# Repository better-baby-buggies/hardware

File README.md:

# hardware
Hardware designs for the PCB's in our Better Baby Buggy!

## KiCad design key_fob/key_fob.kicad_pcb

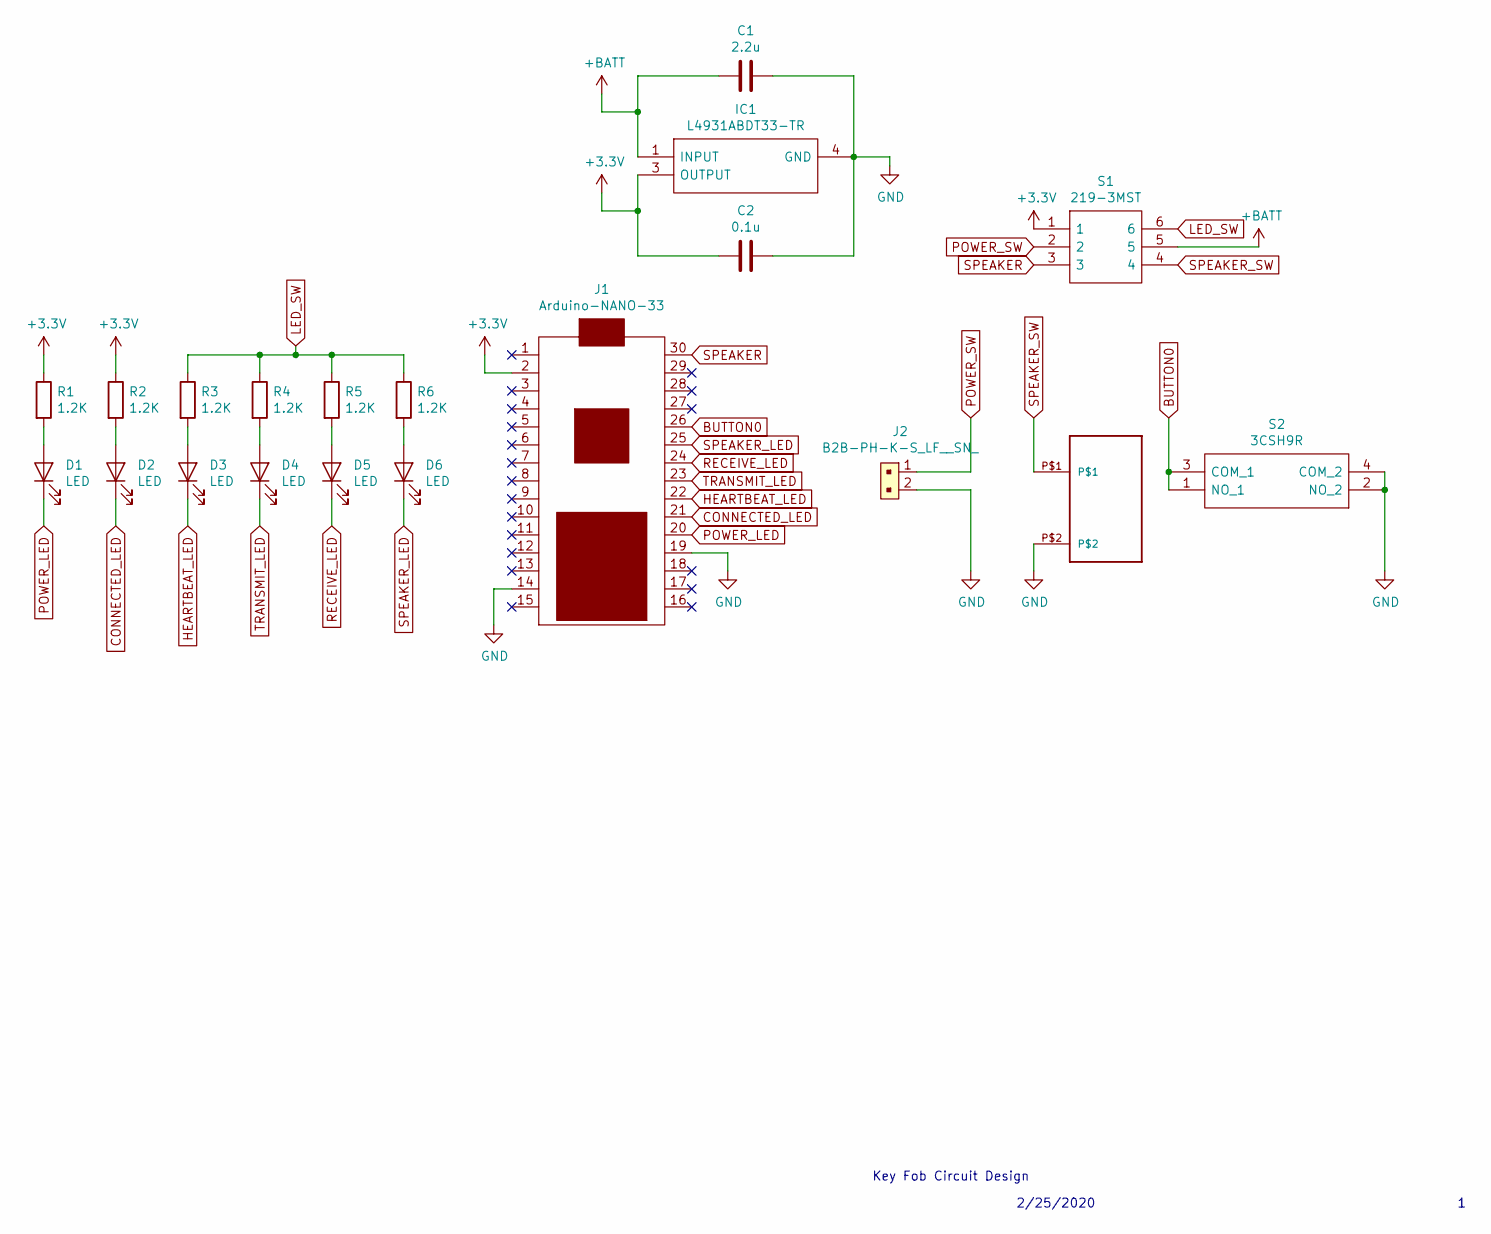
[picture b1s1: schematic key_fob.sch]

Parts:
C1: 2.2u; C_0603_1608Metric_Pad1.05x0.95mm_HandSolder
C2: 0.1u; C_0603_1608Metric_Pad1.05x0.95mm_HandSolder
D1, D2: LED; LED_D5.0mm
D3, D4, D5, D6: LED; LED_1206_3216Metric_Pad1.42x1.75mm_HandSolder
IC1: L4931ABDT33-TR; TO228P972X240-3N; Mouser Part Number 511-L4931ABDT33-TR
J1: Arduino-NANO-33; NANO_33_Footprint_SMD_Castell
J2: B2B-PH-K-S_LF__SN_; PinHeader_1x2_P2mm_Drill1mm; MPN B2B-PH-K-S(LF)(SN); Digi-Key_PN 455-1704-ND
R1, R2, R3, R4, R5, R6: 1.2K; R_0603_1608Metric_Pad1.05x0.95mm_HandSolder
S1: 219-3MST; SOP254P991X385-6N; Mouser Part Number 774-2193MST
S2: 3CSH9R; Mouser Part Number 642-3CSH9R
U1: PS1240P02BT

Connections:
+3V3: C2.1, IC1.3 (OUTPUT), J1.2, R1.1, R2.1, S1.1
+BATT: C1.2, IC1.1 (INPUT), S1.5
BUTTON0: J1.26, S2.1 (NO_1), S2.3 (COM_1)
CONNECTED_LED: D2.1 (K), J1.21
GND: C1.1, C2.2, IC1.4 (GND), J1.14, J1.19, J2.2, S2.2 (NO_2), S2.4 (COM_2), U1.P$2
HEARTBEAT_LED: D3.1 (K), J1.22
LED_SW: R3.1, R4.1, R5.1, R6.1, S1.6
unnamed: D1.2 (A), R1.2
unnamed: D2.2 (A), R2.2
unnamed: D3.2 (A), R3.2
unnamed: D4.2 (A), R4.2
unnamed: D5.2 (A), R5.2
unnamed: D6.2 (A), R6.2
POWER_LED: D1.1 (K), J1.20
POWER_SW: J2.1, S1.2
RECEIVE_LED: D5.1 (K), J1.24
SPEAKER: J1.30, S1.3
SPEAKER_LED: D6.1 (K), J1.25
SPEAKER_SW: S1.4, U1.P$1
TRANSMIT_LED: D4.1 (K), J1.23

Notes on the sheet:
Key Fob Circuit Design
2/25/2020

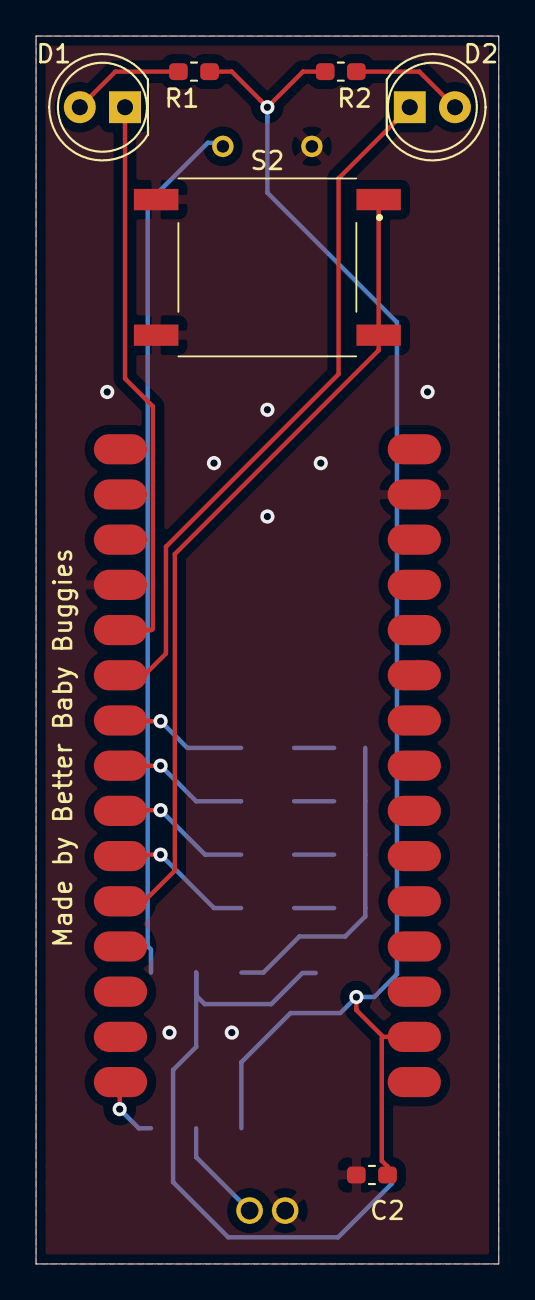
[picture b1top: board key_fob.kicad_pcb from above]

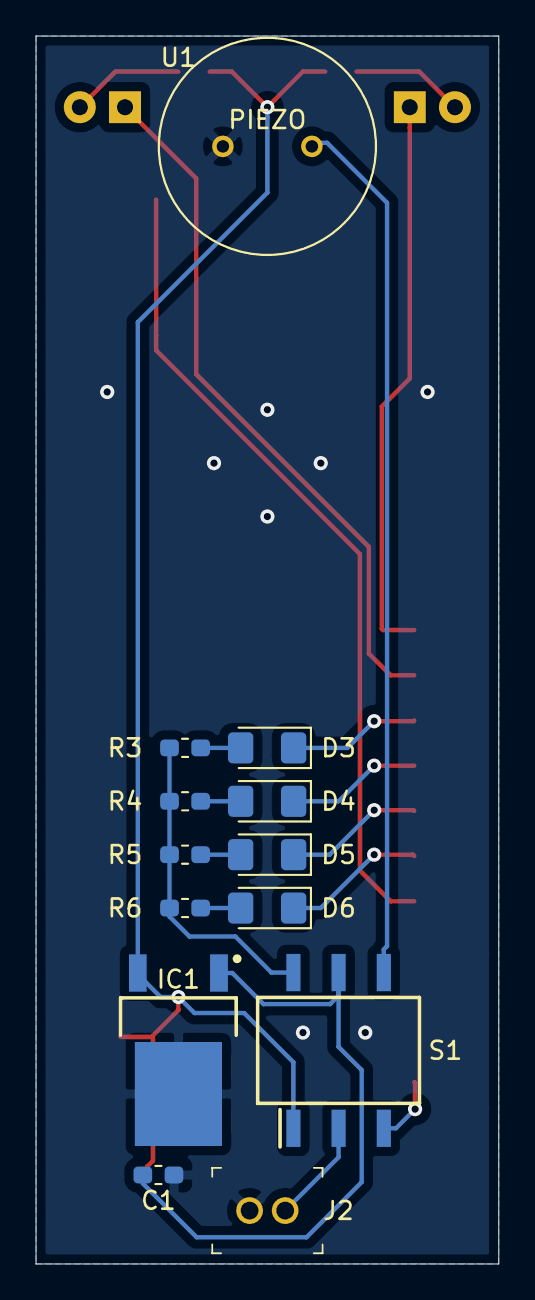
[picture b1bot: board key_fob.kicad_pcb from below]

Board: 2 copper layers, 26.0 x 69.0 mm, 20 parts (13 on the bottom side), 20 nets.

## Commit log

2020-01-28 Started project and added Nano_33 footprint library
2020-01-28 Started Schmatic for key_fob
2020-01-30 Added key fob pdf
2020-01-30 Updated schmatic to include alarm off button
2020-02-14 Added footprint and symbol library for some of the parts picked out
2020-02-18 Added Mosfets for External LEDs
2020-02-20 Linked all symbols to footprints
2020-02-25 Changed external leds back to not using MOSFET
2020-02-25 Filled out title block and printed rev1 pdf
2020-02-25 Imported schematic into pcb layout
2020-03-03 Got some stuff started for key fod pcb
2020-03-03 Added .gitignore and removed files
2020-03-03 First try at placing parts on PCB (no routing)
2020-03-03 Changed board size to 26x69mm
2020-03-03 Routed everything except the ground connections?=
2020-03-03 Cleaned up and mostly finished design
